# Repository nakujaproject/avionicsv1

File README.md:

# avionicsv1

Repository to store sensor code.

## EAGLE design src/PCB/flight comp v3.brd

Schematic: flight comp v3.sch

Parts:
C1, C2: C2,5-3; C2.5-3
IC1: 7805TV; TO220V
SG1: B/C11L
SV1: MA03-1
U1: GY-521MPU6050; GY-521
U$1: ESP32DEVKITC; ESP32-DEVKITC
U$2: MICROSDADAPTER
U$3: BMP180
U$4: DBCONN-1X2
U$5, U$6: JST-PH_2-PIN_HEADER; JST_B2B-PH_HEADER

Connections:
3V3: U$1.1 (3V3), U$3.VIN
5V: C2.1, IC1.3 (VO), SV1.2, U1.VCC, U$1.19 (5V), U$2.VCC1 (VCC)
BUZZER: SG1.1, U$1.30 (IO18)
CS: U$1.13 (IO12), U$2.CS1 (CS)
EN: U$1.2 (EN), U$6.P1 (1)
GND: C1.2, C2.2, IC1.2 (GND), SG1.2, SV1.3, U1.GND, U$1.14 (GND), U$1.38 (GND), U$2.GND1 (GND), U$3.GND, U$4.P0, U$5.P1 (1), U$6.P2 (2)
MISO: U$1.10 (IO26), U$2.MISO1 (MISO)
MOSI: U$1.11 (IO27), U$2.MOSI1 (MOSI)
unnamed: C1.1, IC1.1 (VI), U$4.P1
PWM: SV1.1, U$1.31 (IO19)
RST: U$1.15 (IO13), U$5.P2 (2)
SCK: U$1.12 (IO14), U$2.SCK1 (SCK)
SCL: U1.SCL, U$1.36 (IO22), U$3.SCL
SDA: U1.SDA, U$1.33 (IO21), U$3.SDA

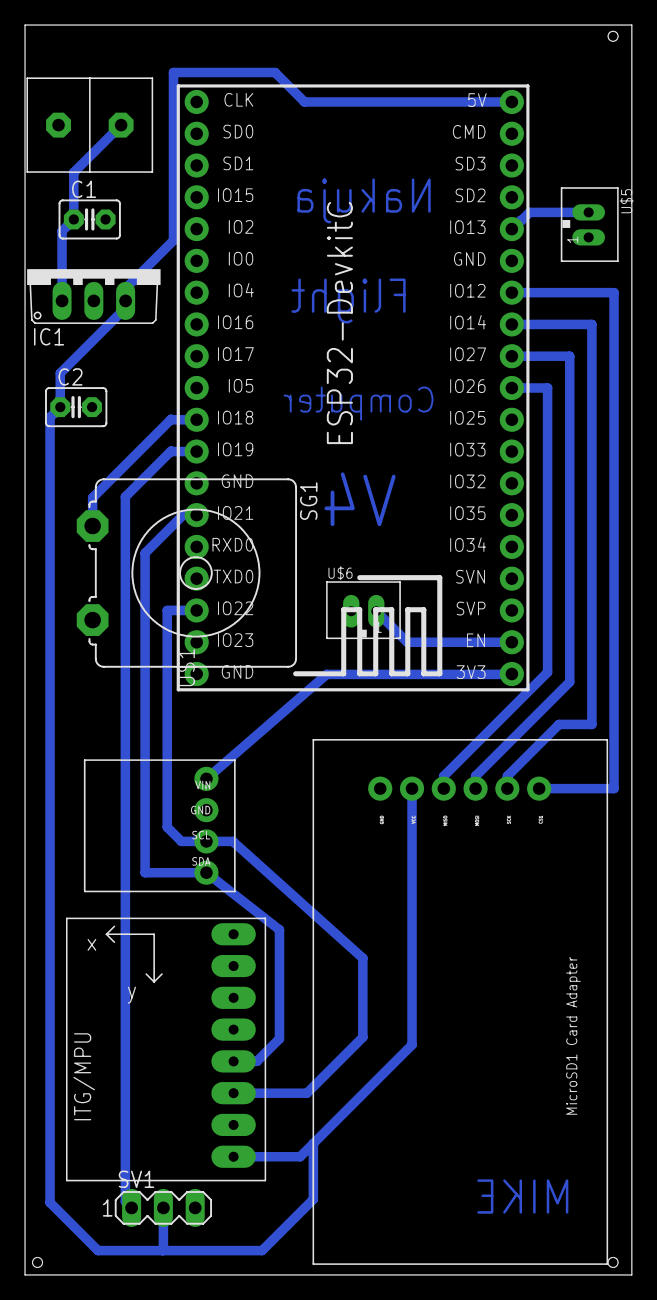
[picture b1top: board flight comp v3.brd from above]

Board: 2 copper layers, 48.5 x 99.9 mm, 12 parts (0 on the bottom side), 14 nets.

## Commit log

2021-03-08 README
2021-03-08 Programming the BMP180
2021-03-17 Combined avionics code
2021-03-17 Testing the bmp 180
2021-03-17 Servo program for parachute deployment
2021-03-17 Program to kickstart ignition
2021-03-18 Kalman filter with the BMP 180
2021-03-18 MPU6050 code to read acceleration and orientation
2021-03-21 Adding relay funciton
2021-03-21 Comparing 5 sensor noise filters
2021-03-24 Code used with processing.
    I added the code I had made some time back using the MPU6050 and processing software.
    It shows a graphical interface of the rocket and models in real time the orientation.
2021-03-27 Program for parachute testing and data collection
2021-03-27 Rearranging
2021-03-27 MPU code with somewhat reasonable acceleration values
2021-03-30 Kalman bmp mpu implementation
2021-03-30 Fixed matrix dimension issues
2021-03-31 Kalman filtered accelerometer data in csv
2021-03-31 Kalman filtered altitude data
2021-03-31 ✨ NEW FEATURE: BMP280 sensor fusion
2021-03-31 video recodring to sd card with esp32-cam
2021-03-31 saving pictures to esp32-cam sd card
2021-04-04 :truck: Organise files
2021-04-04 :sparkles: Single var kalman filter for bmp
2021-04-06 recording video or a specified period and saving it to file
2021-04-06 ✨ NEW FEATURE: Apogee
2021-04-06 🚑 HOTFIX: closes nakujaproject/intern/issues/76
2021-04-07 Changing output values to x_hat
2021-04-07 ✨ NEW FEATURE:
2021-04-07 Organising
2021-04-07 Changing ouptut matrix
2021-04-07 ✨ NEW FEATURE: Fix sd
2021-04-07 🚑 HOTFIX:
2021-04-07 Logging altitude, velocity and acceleration data to sd
2021-04-07 Adding index and raw values
2021-04-07 Stationary altitude and acceleration data
2021-04-07 Print out altitude, velocity and acceleration
2021-04-08 ✨ NEW FEATURE: Logging for different accelerations
2021-04-09 Altitude and acceleration data
2021-04-11 🔨 REFACTOR: Clean up repo
2021-04-11 🐛 BUG: Remove harsh compliance
2021-04-11 🐛 BUG:
2021-04-11 🐛 BUG: 🔨 REFACTOR:
2021-04-12 Removing bug
2021-04-12 Calling the apogee detection functions
2021-04-14 Flight computer PCB design
2021-04-15 🚀 RELEASE: Apogee detection
2021-04-15 🚑 HOTFIX: Fromstm32 to esp
2021-04-18 📝 DOC: BMP180 docs
2021-04-18 📝 DOC: init commit
2021-04-18 🐛 BUG: Image directories
2021-04-19 Flight data from the water rocket
2021-04-19 Water rocket flight data
2021-04-19 Reorganizing
2021-04-20 Data logging code allowing for change of default SPI pins
2021-04-20 Version 2
2021-04-20 Version 3
2021-04-20 Motor test
2021-04-20 Adding servo function
2021-04-20 Flight data 20th of April
2021-04-21 GPS data
2021-04-22 📝 DOC:
2021-04-22 Using 2 cores
2021-04-23 remove unnecessary declaration
2021-04-23 PCB schematic
2021-04-23 PDF for the schematic
2021-04-25 Removing delay
2021-04-25 PCB board
2021-04-25 Time taken to perform different functions
2021-04-26 💄 UI: Format document
2021-04-27 🚑 HOTFIX: Delete unnecessary files
2021-04-27 🔨 REFACTOR: Seperate variables
2021-04-27 🚀 RELEASE: Launchpad control
2021-04-27 💄 UI: Format
2021-04-27 Moving PCB files to PCB repo
2021-04-27 🚑 HOTFIX: Change system matrix
2021-04-27 Display kalman and altitude
2021-04-29 beeping buzzer
2021-04-30 Bash scripts
2021-04-30 Setting servo pin as output
2021-04-30 Loop time
2021-04-30 🚀 RELEASE: Launch pad configs
2021-04-30 Code
2021-04-30 Comparing filtered and real values
2021-04-30 Reducing lift off and apogee deviation
2021-04-30 Changing to ay
2021-04-30 Final
2021-05-01 Buzzing after getting logging command
2021-05-01 🚑 HOTFIX: Change output response
2021-05-01 Adding server to restart logging
2021-05-02 🔧 CONFIG: Gitignore
2021-05-03 Final version
2021-05-03 Final version_1
2021-05-05 Flight data
2021-05-06 Changing to csv
2021-05-06 Cleaning up Data directory
2021-05-06 Changes after failed recovery
2021-05-08 07-05 Launch
2021-05-12 Improving buzzing function
2021-05-12 Moving GPS code to N2
2021-05-12 Rearranging functions and adding comments
2021-05-15 Changing q values
2021-05-16 Update code

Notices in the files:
parts and their libraries:
SparkFun-Aesthetics: Licensing: Creative Commons ShareAlike 4.0 International - https://creativecommons.org/licenses/by-sa/4.0
